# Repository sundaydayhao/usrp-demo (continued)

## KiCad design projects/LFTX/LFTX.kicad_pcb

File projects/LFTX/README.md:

# LFTX

低频发射板，保留模拟链路和电源变换；磁珠值按原 BOM 修正。

使用 KiCad 10.0.5 验证。打开 `LFTX.kicad_pro`，工程内包含可编辑原理图、PCB、`USRP.kicad_sym`、`USRP.pretty` 和本地库表。多页工程从同名顶层原理图进入。

ERC 错误 0，ERC 警告 2；DRC 错误 0，DRC 警告 3，未连接 0。详见检查报告。

- [采购 BOM](BOM-sourcing.csv)：实际 LCSC 编码仅在已核对型号与封装时填写；空白项仍需选型/询价。
- [预览](preview/)：原理图和 PCB 各铜层图。
- [完整设计说明](../../DESIGN_NOTES.md)：原始资料差异、USRP1 机械接口、RF 匹配、叠层、装配和样板验证限制。
- [检查证据](../../verification/LFTX/)：ERC、DRC、网表、封装与射频检查记录。

必须连同设计说明审查。TVRX2/WBX 使用焊盘内过孔，应评审塞孔盖铜工艺。PCB 上无源器件位号可在 F.Fab/B.Fab 装配层查看。未进行实物功能或射频指标测试。

## 3D 模型

PCB 和本地封装库已绑定工程内的 `3dmodels/`，无需额外安装模型库。请保留整个工程目录。

- [正反面 3D 预览](preview/3d-views.pdf)
- [模型来源、简化模型与尺寸限制](../../3D_MODELS.md)

PMC 插座是简化外形模型；TVRX 的调谐模块也为简化外形，高度按 15 mm 示意，未包含外接 F 连接器。3D 外形补充没有修改电路、焊盘或 RF 走线。

## 2026-09-14 器件更新

EEPROM 已改为 AT24C02，完整料号 Microchip AT24C02C-SSHM-T（C6203）；编程页长 8 字节，不可跨页写入。原有 SOIC-8 焊盘和 3D 模型沿用。阻容感允许按价格、库存和交期选择国内或国际品牌，具体已选料号及待锁定行见本工程 BOM-sourcing.csv；更新证据见 [器件更新说明](../../COMPONENT_UPDATE.md)。

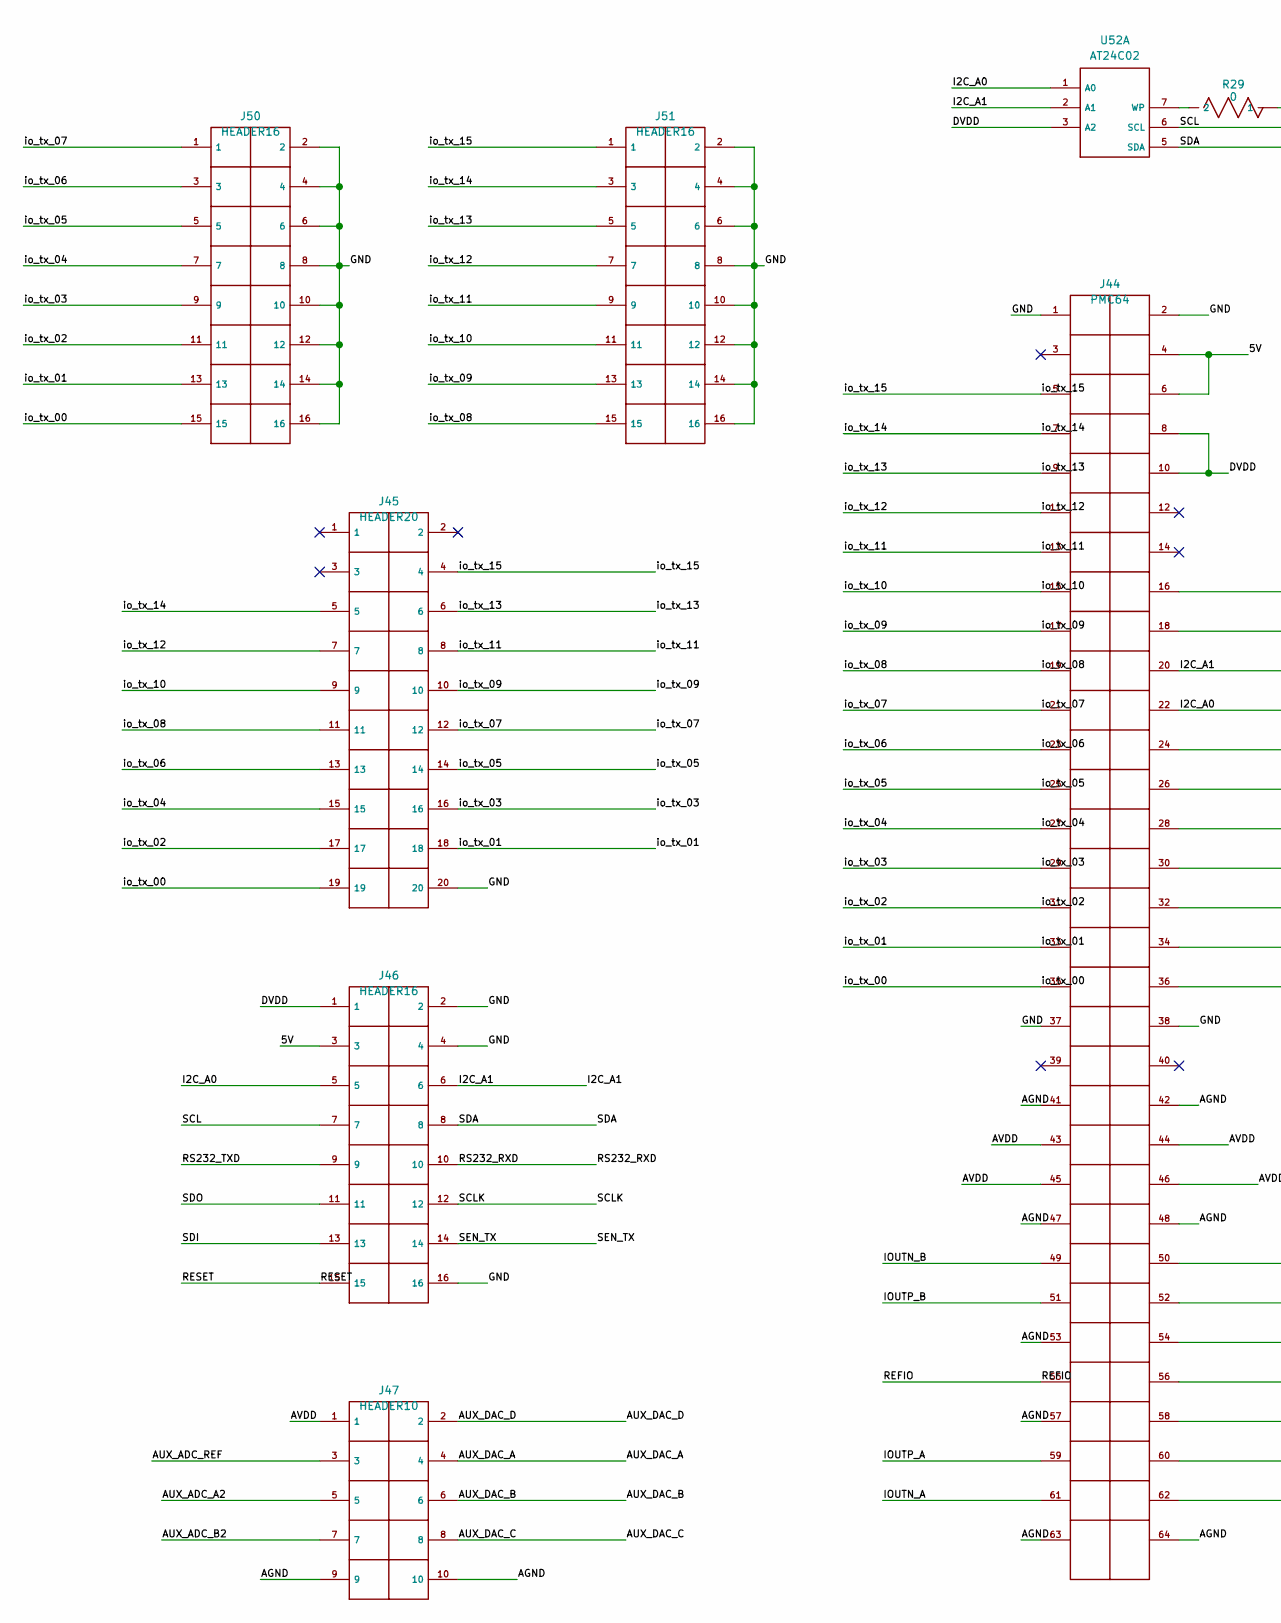
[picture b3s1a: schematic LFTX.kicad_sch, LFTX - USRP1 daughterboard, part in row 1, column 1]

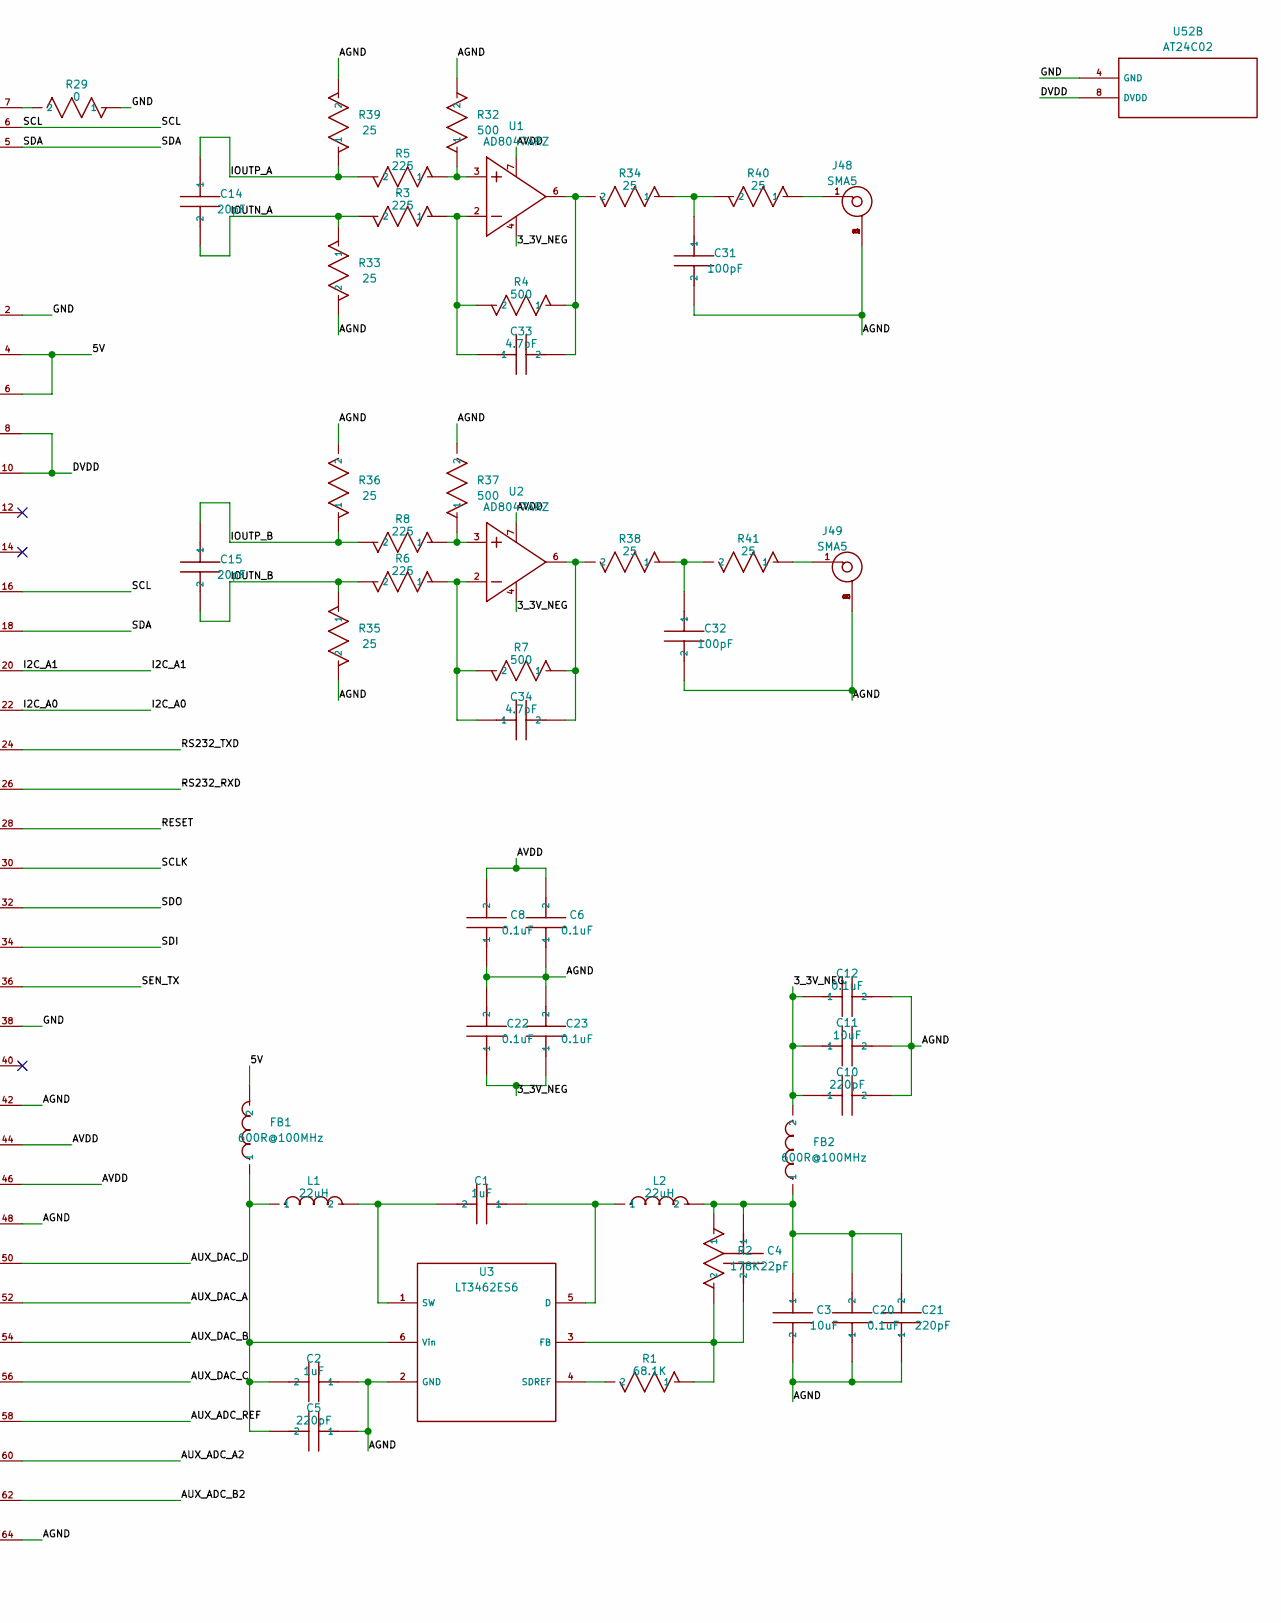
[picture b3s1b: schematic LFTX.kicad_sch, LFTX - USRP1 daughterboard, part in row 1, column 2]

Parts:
C1: 1uF; C1
C2: 1uF; C2
C3: 10uF; C3
C4: 22pF; C4
C5: 220pF; C5
C6: 0.1uF; C6; MPN 0603B104K500NT; LCSC C30926
C8: 0.1uF; C8; MPN 0603B104K500NT; LCSC C30926
C10: 220pF; C10
C11: 10uF; C11
C12: 0.1uF; C12; MPN 0603B104K500NT; LCSC C30926
C14: 20pF; C14
C15: 20pF; C15
C20: 0.1uF; C20; MPN 0603B104K500NT; LCSC C30926
C21: 220pF; C21
C22: 0.1uF; C22; MPN 0603B104K500NT; LCSC C30926
C23: 0.1uF; C23; MPN 0603B104K500NT; LCSC C30926
C31: 100pF; C31
C32: 100pF; C32
C33: 4.7pF; C33
C34: 4.7pF; C34
FB1: 600R@100MHz; FB1; MPN GZ3216D601TF
FB2: 600R@100MHz; FB2; MPN GZ3216D601TF
J44: PMC64; J44
J45: HEADER20; J45
J46: HEADER16; J46
J47: HEADER10; J47
J48: SMA5; J48
J49: SMA5; J49
J50: HEADER16; J50
J51: HEADER16; J51
L1: 22uH; L1
L2: 22uH; L2
R1: 68.1K; R1
R2: 178K; R2
R3: 225; R3
R4: 500; R4
R5: 225; R5
R6: 225; R6
R7: 500; R7
R8: 225; R8
R29: 0; R29; MPN 0603WAF0000T5E; LCSC C21189
R32: 500; R32
R33: 25; R33
R34: 25; R34
R35: 25; R35
R36: 25; R36
R37: 500; R37
R38: 25; R38
R39: 25; R39
R40: 25; R40
R41: 25; R41
U1: AD8047ARZ; U1; MPN AD8047ARZ
U2: AD8047ARZ; U2; MPN AD8047ARZ
U3: LT3462ES6; U3; MPN LT3462ES6
U52: AT24C02; U52; MPN AT24C02C-SSHM-T; LCSC C6203

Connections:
/3_3V_NEG: C10.1, C11.1, C12.1, C22.1, C23.1, FB2.2, U1.4, U2.4
/5V: FB1.2, J44.4, J44.6, J46.3
/AGND: C2.1, C3.2, C5.1, C6.1, C8.1, C10.2, C11.2, C12.2, C20.1, C21.1, C22.2, C23.2, C31.2, C32.2, J44.41, J44.42, J44.47, J44.48, J44.53, J44.57, J44.63, J44.64, J47.9, J47.10, J48.2, J48.3, J48.4, J48.5, J49.2, J49.3, J49.4, J49.5, R32.2, R33.2, R35.2, R36.2, R37.2, R39.2, U3.2 (GND)
/AUX_ADC_A2: J44.60, J47.5
/AUX_ADC_B2: J44.62, J47.7
/AUX_ADC_REF: J44.58, J47.3
/AUX_DAC_A: J44.52, J47.4
/AUX_DAC_B: J44.54, J47.6
/AUX_DAC_C: J44.56, J47.8
/AUX_DAC_D: J44.50, J47.2
/AVDD: C6.2, C8.2, J44.43, J44.44, J44.45, J44.46, J47.1, U1.7, U2.7
/DVDD: J44.8, J44.10, J46.1, U52.3 (A2), U52.8 (DVDD)
/GND: J44.1, J44.2, J44.37, J44.38, J45.20, J46.2, J46.4, J46.16, J50.2, J50.4, J50.6, J50.8, J50.10, J50.12, J50.14, J50.16, J51.2, J51.4, J51.6, J51.8, J51.10, J51.12, J51.14, J51.16, R29.1, U52.4 (GND)
/I2C_A0: J44.22, J46.5, U52.1 (A0)
/I2C_A1: J44.20, J46.6, U52.2 (A1)
/IOUTN_A: C14.2, J44.61, R3.2, R33.1
/IOUTN_B: C15.2, J44.49, R6.2, R35.1
/IOUTP_A: C14.1, J44.59, R5.2, R39.1
/IOUTP_B: C15.1, J44.51, R8.2, R36.1
/REFIO: J44.55
/RESET: J44.28, J46.15
/RS232_RXD: J44.26, J46.10
/RS232_TXD: J44.24, J46.9
/SCL: J44.16, J46.7, U52.6 (SCL)
/SCLK: J44.30, J46.12
/SDA: J44.18, J46.8, U52.5 (SDA)
/SDI: J44.34, J46.13
/SDO: J44.32, J46.11
/SEN_TX: J44.36, J46.14
/io_tx_00: J44.35, J45.19, J50.15
/io_tx_01: J44.33, J45.18, J50.13
/io_tx_02: J44.31, J45.17, J50.11
/io_tx_03: J44.29, J45.16, J50.9
/io_tx_04: J44.27, J45.15, J50.7
/io_tx_05: J44.25, J45.14, J50.5
/io_tx_06: J44.23, J45.13, J50.3
/io_tx_07: J44.21, J45.12, J50.1
/io_tx_08: J44.19, J45.11, J51.15
/io_tx_09: J44.17, J45.10, J51.13
/io_tx_10: J44.15, J45.9, J51.11
/io_tx_11: J44.13, J45.8, J51.9
/io_tx_12: J44.11, J45.7, J51.7
/io_tx_13: J44.9, J45.6, J51.5
/io_tx_14: J44.7, J45.5, J51.3
/io_tx_15: J44.5, J45.4, J51.1
unnamed: C3.1, C4.1, C20.2, C21.2, FB2.1, L2.2, R2.1
unnamed: C31.1, R34.1, R40.2
unnamed: C32.1, R38.1, R41.2
unnamed: C33.1, R3.1, R4.2, U1.2
unnamed: C33.2, R4.1, R34.2, U1.6
unnamed: C34.1, R6.1, R7.2, U2.2
unnamed: C34.2, R7.1, R38.2, U2.6
unnamed: J48.1, R40.1
unnamed: J49.1, R41.1
unnamed: R5.1, R32.1, U1.3
unnamed: R8.1, R37.1, U2.3
unnamed: C1.1, L2.1, U3.5 (D)
unnamed: C4.2, R1.1, R2.2, U3.3 (FB)
unnamed: R1.2, U3.4 (SDREF)
unnamed: C1.2, L1.2, U3.1 (SW)
unnamed: C2.2, C5.2, FB1.1, L1.1, U3.6 (Vin)
unnamed: R29.2, U52.7 (WP)

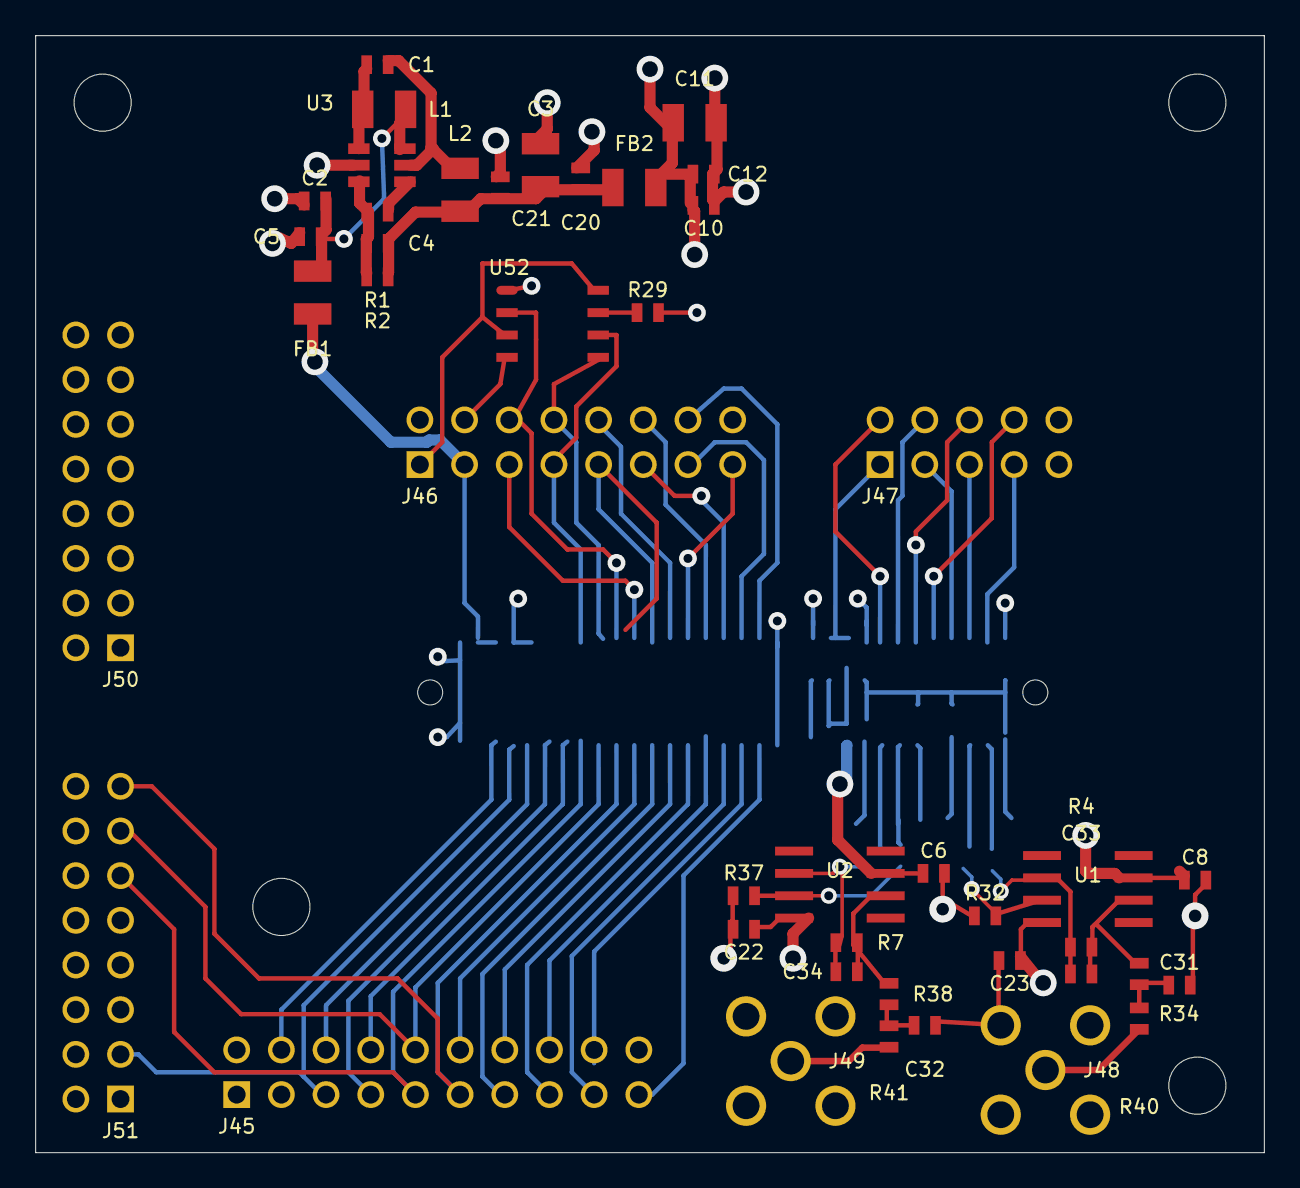
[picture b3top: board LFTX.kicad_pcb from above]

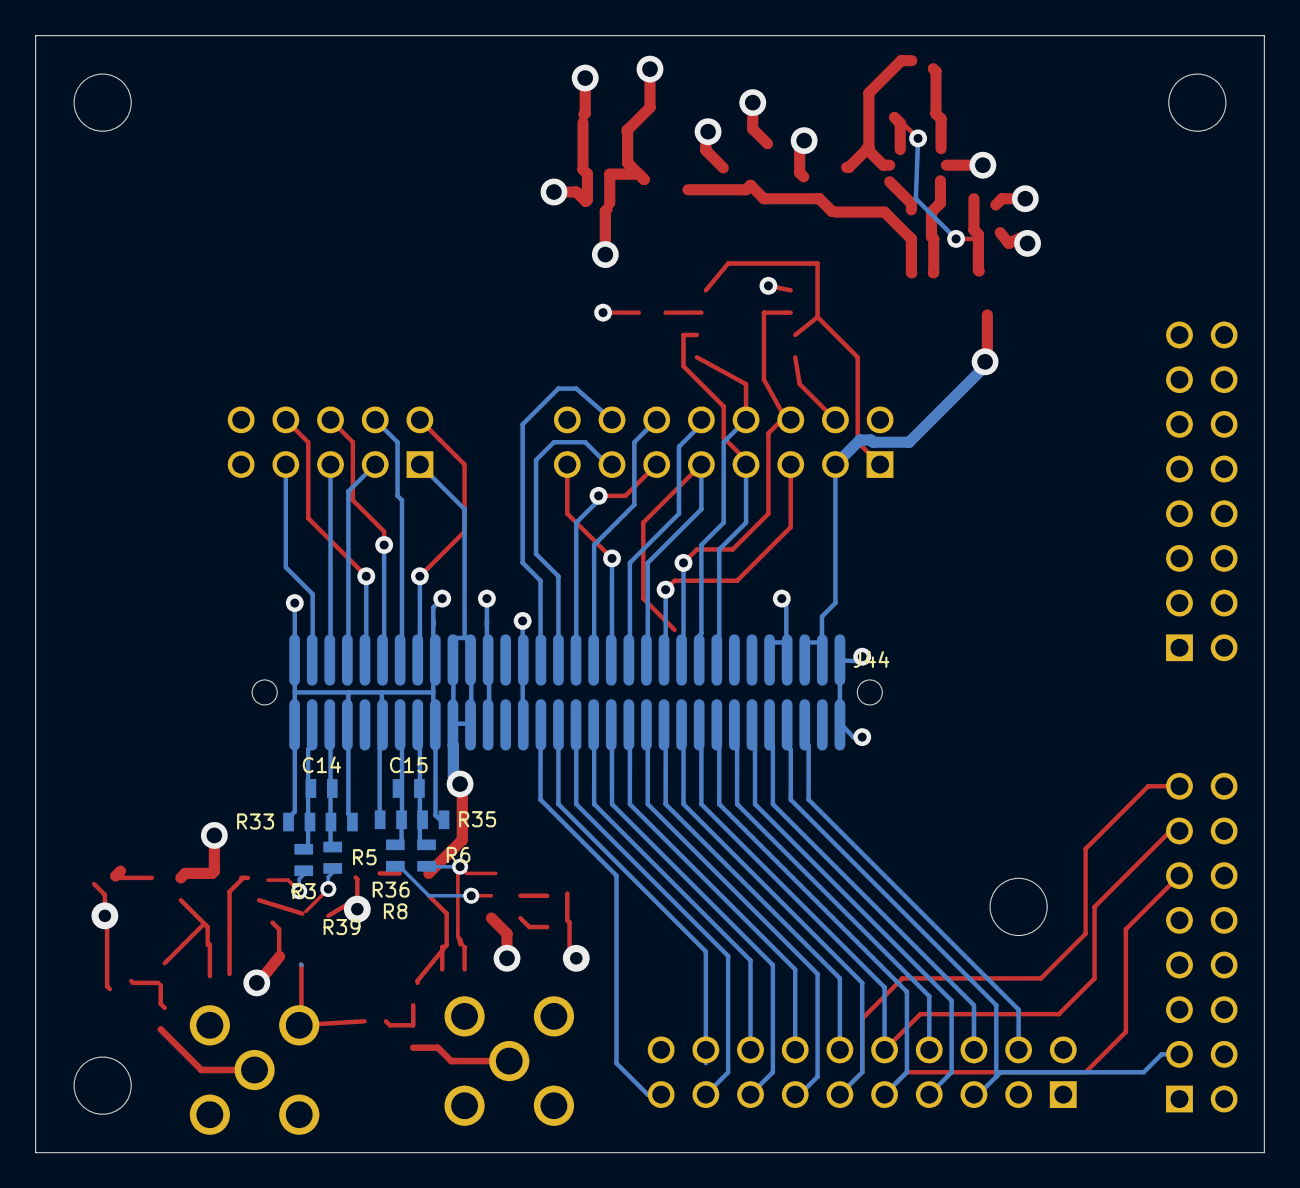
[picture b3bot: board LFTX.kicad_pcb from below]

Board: 4 copper layers, 69.8 x 63.5 mm, 59 parts (11 on the bottom side), 61 nets.

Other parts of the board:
H1, H2, H3, H4: NPTH

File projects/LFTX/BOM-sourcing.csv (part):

Reference,Value,Footprint,Manufacturer,MPN,LCSC,Sourcing_status,Specification,Source_value,Evidence,Approved_brands,Sourcing_policy
C1,1uF,USRP:C1,候选：Murata / TDK / Samsung Electro-Mechanics / Walsin / FH / EYANG,,,规格选型，待锁定料号,按项目焊盘尺寸；RF/匹配/PLL环路优先 C0G；去耦 X7R；耐压 >=16 V；保留原容差,1uF,,Murata / TDK / Samsung Electro-Mechanics / Walsin / FH / EYANG,国产与国际品牌均可；满足参数后比较含税到手价、起订量、库存和交期；换料须复核封装及电气指标
C2,1uF,USRP:C2,候选：Murata / TDK / Samsung Electro-Mechanics / Walsin / FH / EYANG,,,规格选型，待锁定料号,按项目焊盘尺寸；RF/匹配/PLL环路优先 C0G；去耦 X7R；耐压 >=16 V；保留原容差,1uF,,Murata / TDK / Samsung Electro-Mechanics / Walsin / FH / EYANG,国产与国际品牌均可；满足参数后比较含税到手价、起订量、库存和交期；换料须复核封装及电气指标
C3,10uF,USRP:C3,候选：Murata / TDK / Samsung Electro-Mechanics / Walsin / FH / EYANG,,,规格选型，待锁定料号,按项目焊盘尺寸；RF/匹配/PLL环路优先 C0G；去耦 X7R；耐压 >=16 V；保留原容差,10uF,,Murata / TDK / Samsung Electro-Mechanics / Walsin / FH / EYANG,国产与国际品牌均可；满足参数后比较含税到手价、起订量、库存和交期；换料须复核封装及电气指标
C4,22pF,USRP:C4,候选：Murata / TDK / Samsung Electro-Mechanics / Walsin / FH / EYANG,,,规格选型，待锁定料号,按项目焊盘尺寸；RF/匹配/PLL环路优先 C0G；去耦 X7R；耐压 >=16 V；保留原容差,22pF,,Murata / TDK / Samsung Electro-Mechanics / Walsin / FH / EYANG,国产与国际品牌均可；满足参数后比较含税到手价、起订量、库存和交期；换料须复核封装及电气指标
C5,220pF,USRP:C5,候选：Murata / TDK / Samsung Electro-Mechanics / Walsin / FH / EYANG,,,规格选型，待锁定料号,按项目焊盘尺寸；RF/匹配/PLL环路优先 C0G；去耦 X7R；耐压 >=16 V；保留原容差,220pF,,Murata / TDK / Samsung Electro-Mechanics / Walsin / FH / EYANG,国产与国际品牌均可；满足参数后比较含税到手价、起订量、库存和交期；换料须复核封装及电气指标
C6,0.1uF,USRP:C6,FH 风华高科,0603B104K500NT,C30926,已核对目录料号，0603 时采用,0603; 100 nF; X7R; 50 V; +/-10%,0.1uF,https://item.szlcsc.com/31683.html,Murata / TDK / Samsung Electro-Mechanics / Walsin / FH / EYANG,国产与国际品牌均可；满足参数后比较含税到手价、起订量、库存和交期；换料须复核封装及电气指标
C8,0.1uF,USRP:C8,FH 风华高科,0603B104K500NT,C30926,已核对目录料号，0603 时采用,0603; 100 nF; X7R; 50 V; +/-10%,0.1uF,https://item.szlcsc.com/31683.html,Murata / TDK / Samsung Electro-Mechanics / Walsin / FH / EYANG,国产与国际品牌均可；满足参数后比较含税到手价、起订量、库存和交期；换料须复核封装及电气指标
C10,220pF,USRP:C10,候选：Murata / TDK / Samsung Electro-Mechanics / Walsin / FH / EYANG,,,规格选型，待锁定料号,按项目焊盘尺寸；RF/匹配/PLL环路优先 C0G；去耦 X7R；耐压 >=16 V；保留原容差,220pF,,Murata / TDK / Samsung Electro-Mechanics / Walsin / FH / EYANG,国产与国际品牌均可；满足参数后比较含税到手价、起订量、库存和交期；换料须复核封装及电气指标
C11,10uF,USRP:C11,候选：Murata / TDK / Samsung Electro-Mechanics / Walsin / FH / EYANG,,,规格选型，待锁定料号,按项目焊盘尺寸；RF/匹配/PLL环路优先 C0G；去耦 X7R；耐压 >=16 V；保留原容差,10uF,,Murata / TDK / Samsung Electro-Mechanics / Walsin / FH / EYANG,国产与国际品牌均可；满足参数后比较含税到手价、起订量、库存和交期；换料须复核封装及电气指标
C12,0.1uF,USRP:C12,FH 风华高科,0603B104K500NT,C30926,已核对目录料号，0603 时采用,0603; 100 nF; X7R; 50 V; +/-10%,0.1uF,https://item.szlcsc.com/31683.html,Murata / TDK / Samsung Electro-Mechanics / Walsin / FH / EYANG,国产与国际品牌均可；满足参数后比较含税到手价、起订量、库存和交期；换料须复核封装及电气指标
C14,20pF,USRP:C14,候选：Murata / TDK / Samsung Electro-Mechanics / Walsin / FH / EYANG,,,规格选型，待锁定料号,按项目焊盘尺寸；RF/匹配/PLL环路优先 C0G；去耦 X7R；耐压 >=16 V；保留原容差,20pF,,Murata / TDK / Samsung Electro-Mechanics / Walsin / FH / EYANG,国产与国际品牌均可；满足参数后比较含税到手价、起订量、库存和交期；换料须复核封装及电气指标
C15,20pF,USRP:C15,候选：Murata / TDK / Samsung Electro-Mechanics / Walsin / FH / EYANG,,,规格选型，待锁定料号,按项目焊盘尺寸；RF/匹配/PLL环路优先 C0G；去耦 X7R；耐压 >=16 V；保留原容差,20pF,,Murata / TDK / Samsung Electro-Mechanics / Walsin / FH / EYANG,国产与国际品牌均可；满足参数后比较含税到手价、起订量、库存和交期；换料须复核封装及电气指标
C20,0.1uF,USRP:C20,FH 风华高科,0603B104K500NT,C30926,已核对目录料号，0603 时采用,0603; 100 nF; X7R; 50 V; +/-10%,0.1uF,https://item.szlcsc.com/31683.html,Murata / TDK / Samsung Electro-Mechanics / Walsin / FH / EYANG,国产与国际品牌均可；满足参数后比较含税到手价、起订量、库存和交期；换料须复核封装及电气指标
C21,220pF,USRP:C21,候选：Murata / TDK / Samsung Electro-Mechanics / Walsin / FH / EYANG,,,规格选型，待锁定料号,按项目焊盘尺寸；RF/匹配/PLL环路优先 C0G；去耦 X7R；耐压 >=16 V；保留原容差,220pF,,Murata / TDK / Samsung Electro-Mechanics / Walsin / FH / EYANG,国产与国际品牌均可；满足参数后比较含税到手价、起订量、库存和交期；换料须复核封装及电气指标
C22,0.1uF,USRP:C22,FH 风华高科,0603B104K500NT,C30926,已核对目录料号，0603 时采用,0603; 100 nF; X7R; 50 V; +/-10%,0.1uF,https://item.szlcsc.com/31683.html,Murata / TDK / Samsung Electro-Mechanics / Walsin / FH / EYANG,国产与国际品牌均可；满足参数后比较含税到手价、起订量、库存和交期；换料须复核封装及电气指标
C23,0.1uF,USRP:C23,FH 风华高科,0603B104K500NT,C30926,已核对目录料号，0603 时采用,0603; 100 nF; X7R; 50 V; +/-10%,0.1uF,https://item.szlcsc.com/31683.html,Murata / TDK / Samsung Electro-Mechanics / Walsin / FH / EYANG,国产与国际品牌均可；满足参数后比较含税到手价、起订量、库存和交期；换料须复核封装及电气指标
C31,100pF,USRP:C31,候选：Murata / TDK / Samsung Electro-Mechanics / Walsin / FH / EYANG,,,规格选型，待锁定料号,按项目焊盘尺寸；RF/匹配/PLL环路优先 C0G；去耦 X7R；耐压 >=16 V；保留原容差,100pF,,Murata / TDK / Samsung Electro-Mechanics / Walsin / FH / EYANG,国产与国际品牌均可；满足参数后比较含税到手价、起订量、库存和交期；换料须复核封装及电气指标
C32,100pF,USRP:C32,候选：Murata / TDK / Samsung Electro-Mechanics / Walsin / FH / EYANG,,,规格选型，待锁定料号,按项目焊盘尺寸；RF/匹配/PLL环路优先 C0G；去耦 X7R；耐压 >=16 V；保留原容差,100pF,,Murata / TDK / Samsung Electro-Mechanics / Walsin / FH / EYANG,国产与国际品牌均可；满足参数后比较含税到手价、起订量、库存和交期；换料须复核封装及电气指标
C33,4.7pF,USRP:C33,候选：Murata / TDK / Samsung Electro-Mechanics / Walsin / FH / EYANG,,,规格选型，待锁定料号,按项目焊盘尺寸；RF/匹配/PLL环路优先 C0G；去耦 X7R；耐压 >=16 V；保留原容差,4.7pF,,Murata / TDK / Samsung Electro-Mechanics / Walsin / FH / EYANG,国产与国际品牌均可；满足参数后比较含税到手价、起订量、库存和交期；换料须复核封装及电气指标
C34,4.7pF,USRP:C34,候选：Murata / TDK / Samsung Electro-Mechanics / Walsin / FH / EYANG,,,规格选型，待锁定料号,按项目焊盘尺寸；RF/匹配/PLL环路优先 C0G；去耦 X7R；耐压 >=16 V；保留原容差,4.7pF,,Murata / TDK / Samsung Electro-Mechanics / Walsin / FH / EYANG,国产与国际品牌均可；满足参数后比较含税到手价、起订量、库存和交期；换料须复核封装及电气指标
FB1,600R@100MHz,USRP:FB1,Sunlord 顺络,GZ3216D601TF,,新选磁珠；需测电源噪声与压降,1206; 600 ohm @100 MHz; 600 mA; DCR <=0.30 ohm,100uH,https://atta.szlcsc.com/upload/public/pdf/source/20151029/14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,Murata / TDK / Coilcraft / Sunlord / FH,国产与国际品牌均可；满足参数后比较含税到手价、起订量、库存和交期；换料须复核封装及电气指标
FB2,600R@100MHz,USRP:FB2,Sunlord 顺络,GZ3216D601TF,,新选磁珠；需测电源噪声与压降,1206; 600 ohm @100 MHz; 600 mA; DCR <=0.30 ohm,100uH,https://atta.szlcsc.com/upload/public/pdf/source/20151029/14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,Murata / TDK / Coilcraft / Sunlord / FH,国产与国际品牌均可；满足参数后比较含税到手价、起订量、库存和交期；换料须复核封装及电气指标
J44,PMC64,USRP:J44,,,,规格选型，待锁定料号,按工程封装和 USRP1 接口核对插合方向、针脚与高度,PMC64,,,
J45,HEADER20,USRP:J45,,,,规格选型，待锁定料号,按工程封装和 USRP1 接口核对插合方向、针脚与高度,HEADER20,,,
J46,HEADER16,USRP:J46,,,,规格选型，待锁定料号,按工程封装和 USRP1 接口核对插合方向、针脚与高度,HEADER16,,,
J47,HEADER10,USRP:J47,,,,规格选型，待锁定料号,按工程封装和 USRP1 接口核对插合方向、针脚与高度,HEADER10,,,
J48,SMA5,USRP:J48,,,,规格选型，待锁定料号,按工程封装和 USRP1 接口核对插合方向、针脚与高度,SMA5,,,
J49,SMA5,USRP:J49,,,,规格选型，待锁定料号,按工程封装和 USRP1 接口核对插合方向、针脚与高度,SMA5,,,
J50,HEADER16,USRP:J50,,,,规格选型，待锁定料号,按工程封装和 USRP1 接口核对插合方向、针脚与高度,HEADER16,,,
J51,HEADER16,USRP:J51,,,,规格选型，待锁定料号,按工程封装和 USRP1 接口核对插合方向、针脚与高度,HEADER16,,,
L1,22uH,USRP:L1,候选：Murata / TDK / Coilcraft / Sunlord / FH,,,规格选型，待锁定料号,RF电感须核对 Q、SRF、DCR 与偏置电流，按原值及容差；磁珠按阻抗曲线选型,22uH,,Murata / TDK / Coilcraft / Sunlord / FH,国产与国际品牌均可；满足参数后比较含税到手价、起订量、库存和交期；换料须复核封装及电气指标
L2,22uH,USRP:L2,候选：Murata / TDK / Coilcraft / Sunlord / FH,,,规格选型，待锁定料号,RF电感须核对 Q、SRF、DCR 与偏置电流，按原值及容差；磁珠按阻抗曲线选型,22uH,,Murata / TDK / Coilcraft / Sunlord / FH,国产与国际品牌均可；满足参数后比较含税到手价、起订量、库存和交期；换料须复核封装及电气指标
R1,68.1K,USRP:R1,候选：YAGEO / Vishay / Panasonic / UNI-ROYAL / FH,,,规格选型，待锁定料号,0603; <=1%; >=0.1 W; 按原值采购；反馈/终端电阻需同批次,68.1K,,YAGEO / Vishay / Panasonic / UNI-ROYAL / FH,国产与国际品牌均可；满足参数后比较含税到手价、起订量、库存和交期；换料须复核封装及电气指标
R2,178K,USRP:R2,候选：YAGEO / Vishay / Panasonic / UNI-ROYAL / FH,,,规格选型，待锁定料号,0603; <=1%; >=0.1 W; 按原值采购；反馈/终端电阻需同批次,178K,,YAGEO / Vishay / Panasonic / UNI-ROYAL / FH,国产与国际品牌均可；满足参数后比较含税到手价、起订量、库存和交期；换料须复核封装及电气指标
R3,225,USRP:R3,候选：YAGEO / Vishay / Panasonic / UNI-ROYAL / FH,,,规格选型，待锁定料号,0603; <=1%; >=0.1 W; 按原值采购；反馈/终端电阻需同批次,225,,YAGEO / Vishay / Panasonic / UNI-ROYAL / FH,国产与国际品牌均可；满足参数后比较含税到手价、起订量、库存和交期；换料须复核封装及电气指标
R4,500,USRP:R4,候选：YAGEO / Vishay / Panasonic / UNI-ROYAL / FH,,,规格选型，待锁定料号,0603; <=1%; >=0.1 W; 按原值采购；反馈/终端电阻需同批次,500,,YAGEO / Vishay / Panasonic / UNI-ROYAL / FH,国产与国际品牌均可；满足参数后比较含税到手价、起订量、库存和交期；换料须复核封装及电气指标
R5,225,USRP:R5,候选：YAGEO / Vishay / Panasonic / UNI-ROYAL / FH,,,规格选型，待锁定料号,0603; <=1%; >=0.1 W; 按原值采购；反馈/终端电阻需同批次,225,,YAGEO / Vishay / Panasonic / UNI-ROYAL / FH,国产与国际品牌均可；满足参数后比较含税到手价、起订量、库存和交期；换料须复核封装及电气指标
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
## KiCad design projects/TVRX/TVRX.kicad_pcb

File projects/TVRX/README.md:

# TVRX

基于 MT4937DI5 调谐模块的接收板。旧模块采购是主要限制。

使用 KiCad 10.0.5 验证。打开 `TVRX.kicad_pro`，工程内包含可编辑原理图、PCB、`USRP.kicad_sym`、`USRP.pretty` 和本地库表。多页工程从同名顶层原理图进入。

ERC 错误 0，ERC 警告 27；DRC 错误 0，DRC 警告 5，未连接 0。详见检查报告。

- [采购 BOM](BOM-sourcing.csv)：实际 LCSC 编码仅在已核对型号与封装时填写；空白项仍需选型/询价。
- [预览](preview/)：原理图和 PCB 各铜层图。
- [完整设计说明](../../DESIGN_NOTES.md)：原始资料差异、USRP1 机械接口、RF 匹配、叠层、装配和样板验证限制。
- [检查证据](../../verification/TVRX/)：ERC、DRC、网表、封装与射频检查记录。

必须连同设计说明审查。TVRX2/WBX 使用焊盘内过孔，应评审塞孔盖铜工艺。PCB 上无源器件位号可在 F.Fab/B.Fab 装配层查看。未进行实物功能或射频指标测试。

## 3D 模型

PCB 和本地封装库已绑定工程内的 `3dmodels/`，无需额外安装模型库。请保留整个工程目录。

- [正反面 3D 预览](preview/3d-views.pdf)
- [模型来源、简化模型与尺寸限制](../../3D_MODELS.md)

PMC 插座是简化外形模型；TVRX 的调谐模块也为简化外形，高度按 15 mm 示意，未包含外接 F 连接器。3D 外形补充没有修改电路、焊盘或 RF 走线。

## 2026-09-14 器件更新

EEPROM 已改为 AT24C02，完整料号 Microchip AT24C02C-SSHM-T（C6203）；编程页长 8 字节，不可跨页写入。原有 SOIC-8 焊盘和 3D 模型沿用。阻容感允许按价格、库存和交期选择国内或国际品牌，具体已选料号及待锁定行见本工程 BOM-sourcing.csv；更新证据见 [器件更新说明](../../COMPONENT_UPDATE.md)。

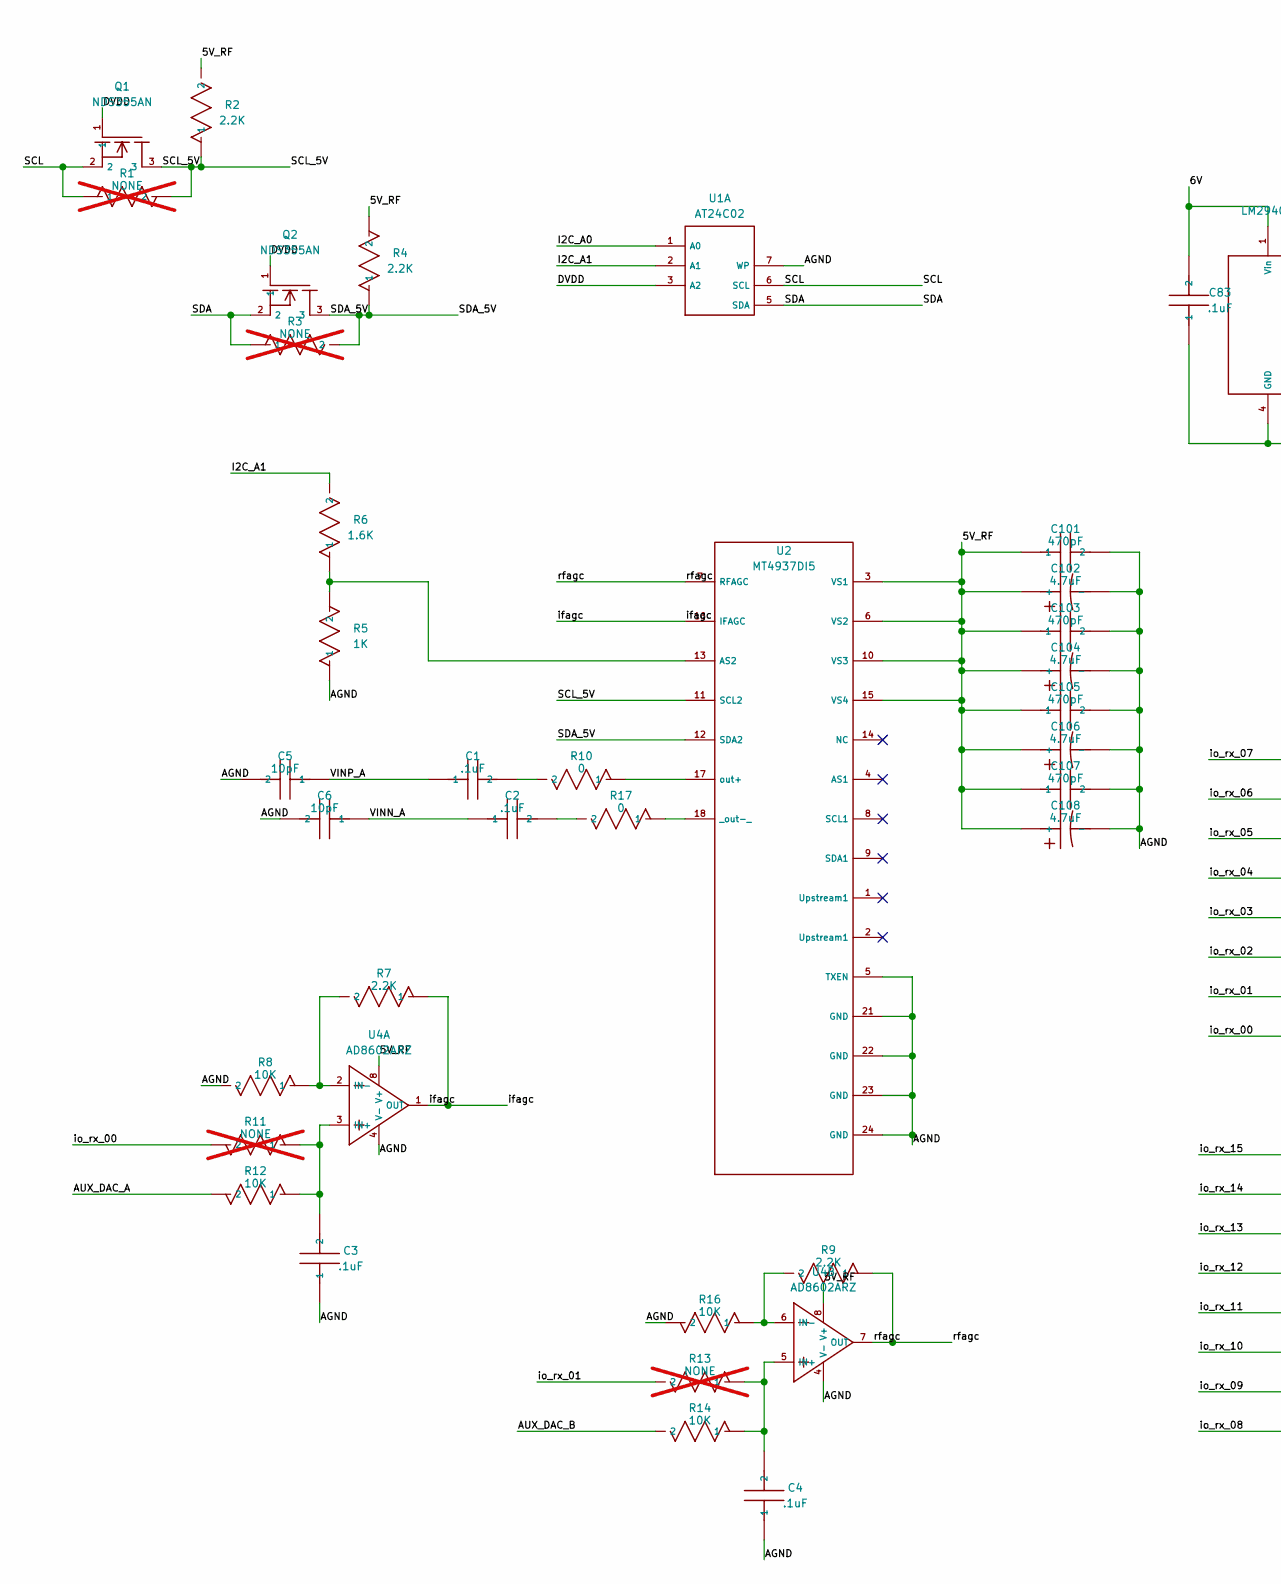
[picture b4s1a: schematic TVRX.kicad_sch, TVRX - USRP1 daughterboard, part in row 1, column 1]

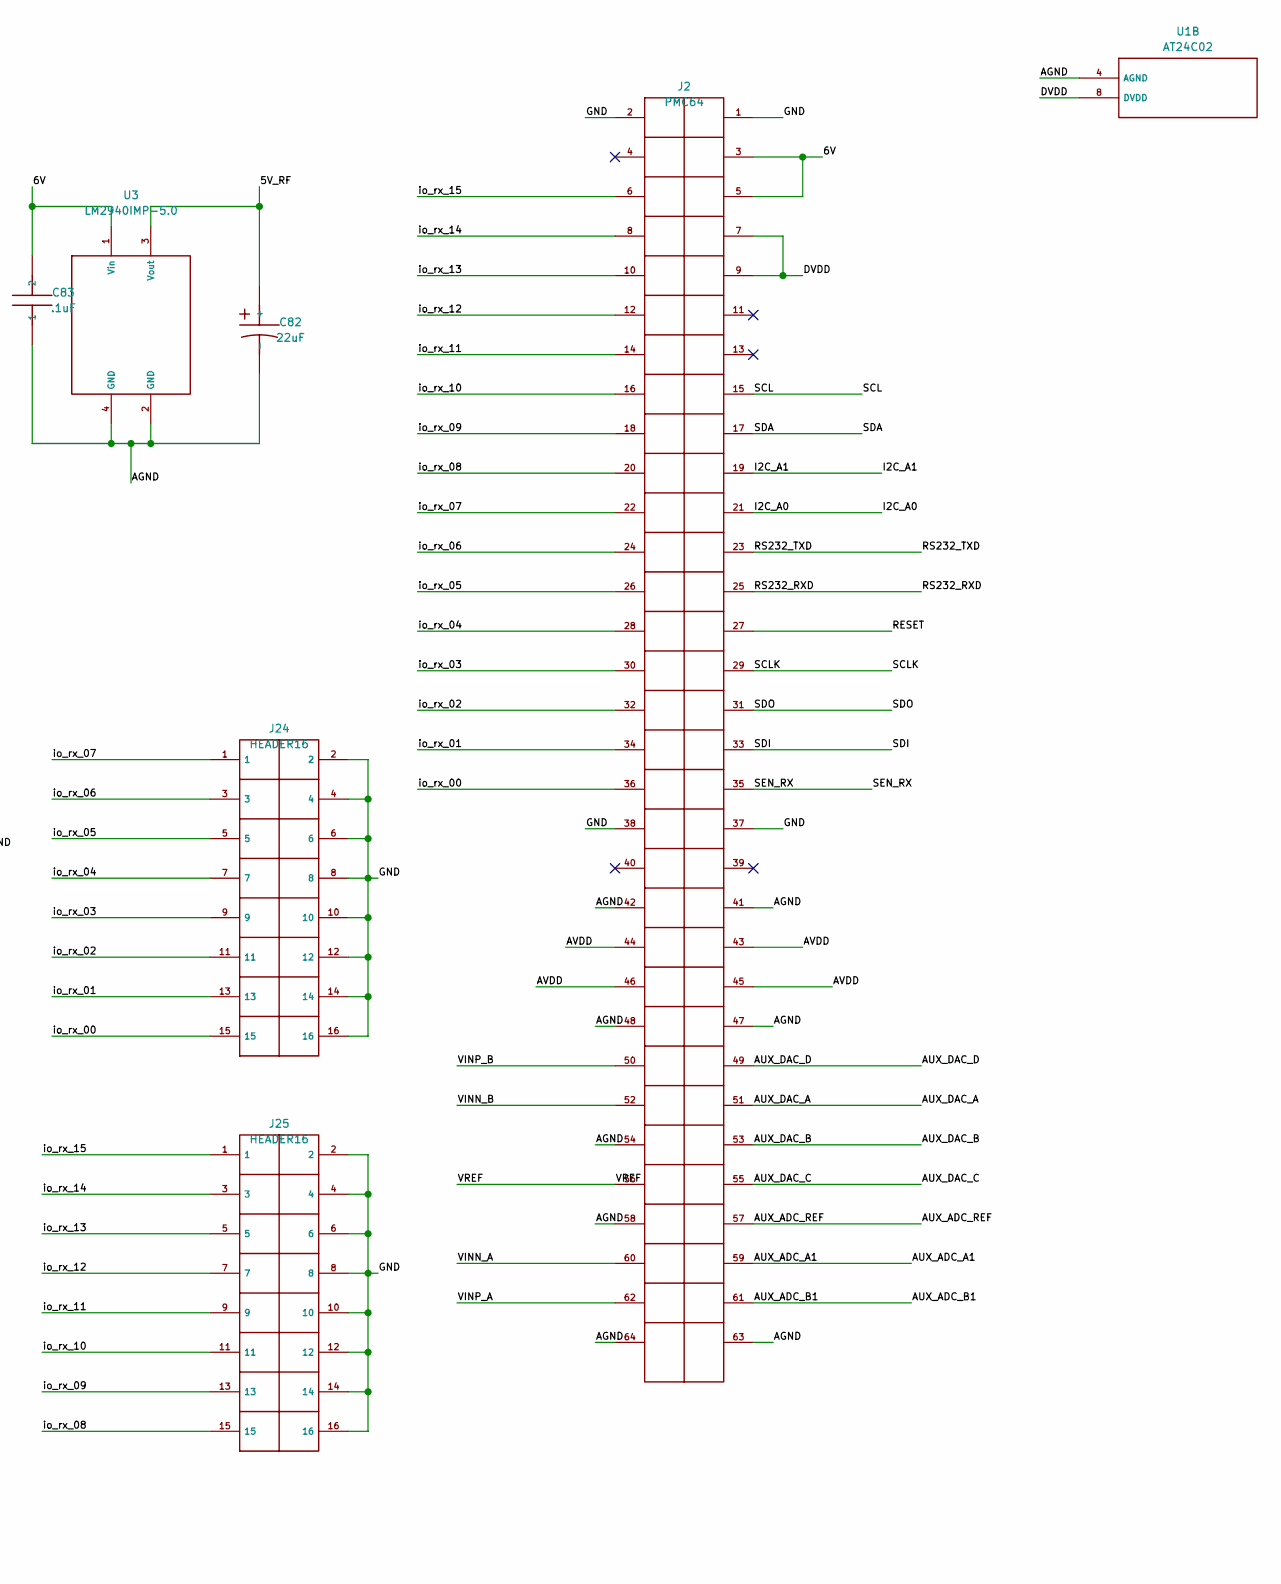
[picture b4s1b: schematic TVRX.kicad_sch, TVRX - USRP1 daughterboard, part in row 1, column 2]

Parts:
C1: .1uF; C1
C2: .1uF; C2
C3: .1uF; C3
C4: .1uF; C4
C5: 10pF; C5; MPN 0603CG100J500NT; LCSC C91367
C6: 10pF; C6; MPN 0603CG100J500NT; LCSC C91367
C82: 22uF; C82
C83: .1uF; C83
C101: 470pF; C101
C102: 4.7uF; C102
C103: 470pF; C103
C104: 4.7uF; C104
C105: 470pF; C105
C106: 4.7uF; C106
C107: 470pF; C107
C108: 4.7uF; C108
J2: PMC64; J2
J24: HEADER16; J24
J25: HEADER16; J25
Q1: NDS355AN; Q1; MPN NDS355AN
Q2: NDS355AN; Q2; MPN NDS355AN
R1: NONE; R1; not fitted
R2: 2.2K; R2
R3: NONE; R3; not fitted
R4: 2.2K; R4
R5: 1K; R5
R6: 1.6K; R6
R7: 2.2K; R7
R8: 10K; R8
R9: 2.2K; R9
R10: 0; R10; MPN 0603WAF0000T5E; LCSC C21189
R11: NONE; R11; not fitted
R12: 10K; R12
R13: NONE; R13; not fitted
R14: 10K; R14
R16: 10K; R16
R17: 0; R17; MPN 0603WAF0000T5E; LCSC C21189
U1: AT24C02; U1; MPN AT24C02C-SSHM-T; LCSC C6203
U2: MT4937DI5; U2; MPN MT4937DI5
U3: LM2940IMP-5.0; U3; MPN LM2940IMP-5.0
U4: AD8602ARZ; U4; MPN AD8602ARZ

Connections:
/5V_RF: C82.1 (+), C101.1, C102.1 (+), C103.1, C104.1 (+), C105.1, C106.1 (+), C107.1, C108.1 (+), R2.2, R4.2, U2.3 (VS1), U2.6 (VS2), U2.10 (VS3), U2.15 (VS4), U3.3 (Vout), U4.8 (V+)
/6V: C83.2, J2.3, J2.5, U3.1 (Vin)
/AGND: C3.1, C4.1, C5.2, C6.2, C82.2 (-), C83.1, C101.2, C102.2 (-), C103.2, C104.2 (-), C105.2, C106.2 (-), C107.2, C108.2 (-), J2.41, J2.42, J2.47, J2.48, J2.54, J2.58, J2.63, J2.64, R5.1, R8.2, R16.2, U1.4 (AGND), U1.7 (WP), U2.5 (TXEN), U2.21 (GND), U2.22 (GND), U2.23 (GND), U2.24 (GND), U3.2 (GND), U3.4 (GND), U4.4 (V-)
/AUX_ADC_A1: J2.59
/AUX_ADC_B1: J2.61
/AUX_ADC_REF: J2.57
/AUX_DAC_A: J2.51, R12.2
/AUX_DAC_B: J2.53, R14.2
/AUX_DAC_C: J2.55
/AUX_DAC_D: J2.49
/AVDD: J2.43, J2.44, J2.45, J2.46
/DVDD: J2.7, J2.9, Q1.1, Q2.1, U1.3 (A2), U1.8 (DVDD)
/GND: J2.1, J2.2, J2.37, J2.38, J24.2, J24.4, J24.6, J24.8, J24.10, J24.12, J24.14, J24.16, J25.2, J25.4, J25.6, J25.8, J25.10, J25.12, J25.14, J25.16
/I2C_A0: J2.21, U1.1 (A0)
/I2C_A1: J2.19, R6.2, U1.2 (A1)
/RESET: J2.27
/RS232_RXD: J2.25
/RS232_TXD: J2.23
/SCL: J2.15, Q1.2, R1.1, U1.6 (SCL)
/SCLK: J2.29
/SCL_5V: Q1.3, R1.2, R2.1, U2.11 (SCL2)
/SDA: J2.17, Q2.2, R3.1, U1.5 (SDA)
/SDA_5V: Q2.3, R3.2, R4.1, U2.12 (SDA2)
/SDI: J2.33
/SDO: J2.31
/SEN_RX: J2.35
/VINN_A: C2.1, C6.1, J2.60
/VINN_B: J2.52
/VINP_A: C1.1, C5.1, J2.62
/VINP_B: J2.50
/VREF: J2.56
/ifagc: R7.1, U2.16 (IFAGC), U4.1 (OUT)
/io_rx_00: J2.36, J24.15, R11.2
/io_rx_01: J2.34, J24.13, R13.2
/io_rx_02: J2.32, J24.11
/io_rx_03: J2.30, J24.9
/io_rx_04: J2.28, J24.7
/io_rx_05: J2.26, J24.5
/io_rx_06: J2.24, J24.3
/io_rx_07: J2.22, J24.1
/io_rx_08: J2.20, J25.15
/io_rx_09: J2.18, J25.13
/io_rx_10: J2.16, J25.11
/io_rx_11: J2.14, J25.9
/io_rx_12: J2.12, J25.7
/io_rx_13: J2.10, J25.5
/io_rx_14: J2.8, J25.3
/io_rx_15: J2.6, J25.1
/rfagc: R9.1, U2.7 (RFAGC), U4.7 (OUT)
unnamed: C1.2, R10.2
unnamed: C2.2, R17.2
unnamed: R5.2, R6.1, U2.13 (AS2)
unnamed: R17.1, U2.18 (_out-_)
unnamed: R10.1, U2.17 (out+)
unnamed: C3.2, R11.1, R12.1, U4.3 (IN+)
unnamed: R7.2, R8.1, U4.2 (IN-)
unnamed: C4.2, R13.1, R14.1, U4.5 (IN+)
unnamed: R9.2, R16.1, U4.6 (IN-)
